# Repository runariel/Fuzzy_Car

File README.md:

# Fuzzy_Car
Planing to make a self driving car by Arduino

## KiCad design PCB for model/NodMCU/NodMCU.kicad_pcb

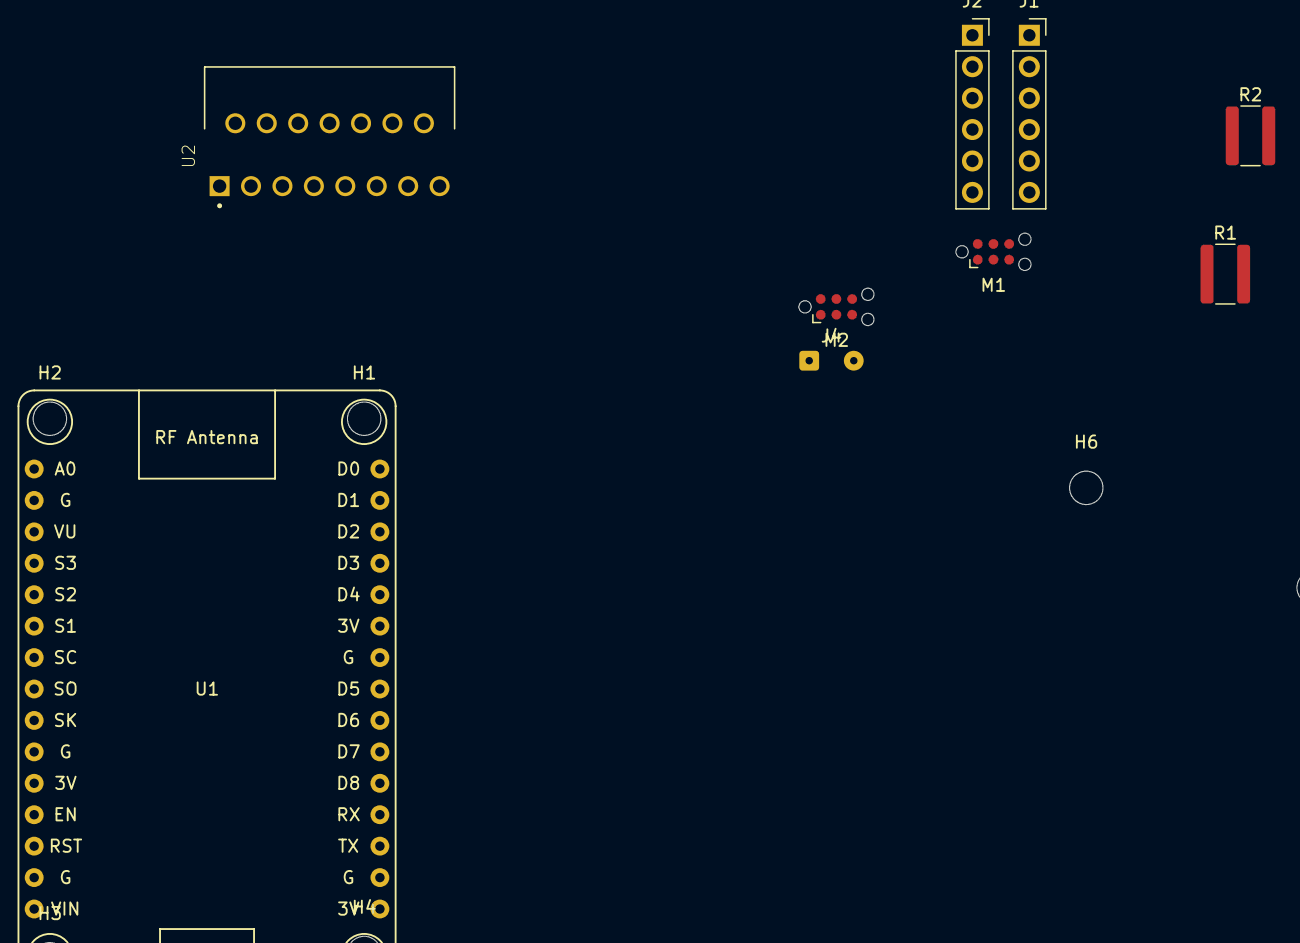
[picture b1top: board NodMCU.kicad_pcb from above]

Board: 2 copper layers, 21 parts (0 on the bottom side), 14 nets, no tracks yet.

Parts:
H1, H2, H3, H4, H5, H6, H7, H8, H9, H10, H11, H12: MountingHole; MountingHole_2.7mm
J1: VL53L0X Left; PinSocket_1x06_P2.54mm_Vertical
J2: VL53L0X Right; PinSocket_1x06_P2.54mm_Vertical
J4: Power supply; SolderWire-0.1sqmm_1x02_P3.6mm_D0.4mm_OD1mm
M1, M2: Motor_DC; Tag-Connect_TC2030-IDC-NL_2x03_P1.27mm_Vertical
R1, R2: 4.7k; R_1218_3246Metric
U1: NodeMCU_1.0_(ESP-12E); NodeMCU1.0(12-E)
U2: L298N; TO127P2020X500X2100-15

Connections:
5V: J1.1, J2.1, J4.1, R1.2, R2.2, U1.15, U2.9
EN_A: U1.23, U2.6
EN_B: U1.22, U2.11
GND: J1.2, J2.2, J4.2, U1.10, U1.14, U1.17, U1.24, U2.8
IN1_IN3: U1.27, U2.5, U2.10
IN2_IN4: U1.21, U2.7, U2.12
unnamed: M1.1, U2.2
unnamed: M1.2, U2.3
unnamed: M2.1, U2.13
unnamed: M2.2, U2.14
SCL: J1.3, J2.3, R1.1, U1.29
SDA: J1.4, J2.4, R2.1, U1.28
XSHUT_Left: J1.6, U1.26
XSHUT_Right: J2.6, U1.20

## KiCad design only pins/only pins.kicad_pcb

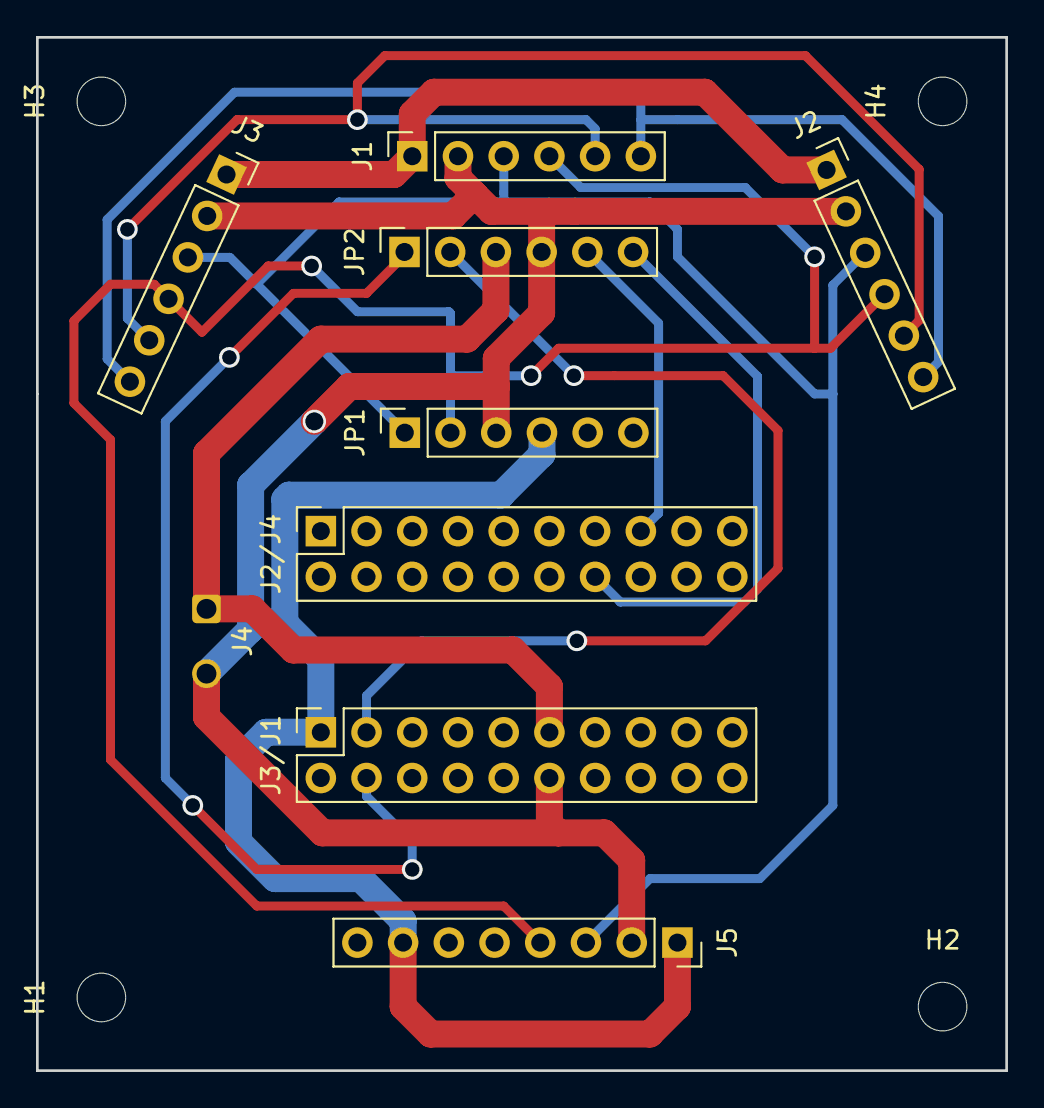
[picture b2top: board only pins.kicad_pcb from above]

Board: 2 copper layers, 53.8 x 57.4 mm, 13 parts (0 on the bottom side), 12 nets.

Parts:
H1, H2, H3, H4: MountingHole; MountingHole_2.7mm
J1, J2, J3: I2c; PinSocket_1x06_P2.54mm_Vertical
J2/J4, J3/J1: PinSocket_2x10_P2.54mm_Vertical
J4: Power supply; SolderWire-0.1sqmm_1x02_P3.6mm_D0.4mm_OD1mm
J5: gyro connector; PinSocket_1x08_P2.54mm_Vertical
JP1, JP2: M06SIP; PinSocket_1x06_P2.54mm_Vertical

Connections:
3.3V: J3/J1.1, J5.1, J5.7, JP1.4
5V: J3/J1.11, J4.1, JP2.3
/A0_RX: J3/J1.3, JP2.2
/A0_TX: J3/J1.4, JP2.1
/GPIO1: J1.5, J2.5, J3.5
/HV3: J2/J4.15, JP2.5
/HV4: J2/J4.14, JP2.6
/LV3: J1.4, J2.4, J3.4, J5.4, JP1.2
/LV4: J1.3, J2.3, J3.3, J5.3, JP1.1
/VIN: J1.1, J2.1, J3.1
/XShutDown: J1.6, J2.6, J3.6
GND: J1.2, J2.2, J3.2, J3/J1.12, J4.2, J5.2, JP1.3, JP2.4

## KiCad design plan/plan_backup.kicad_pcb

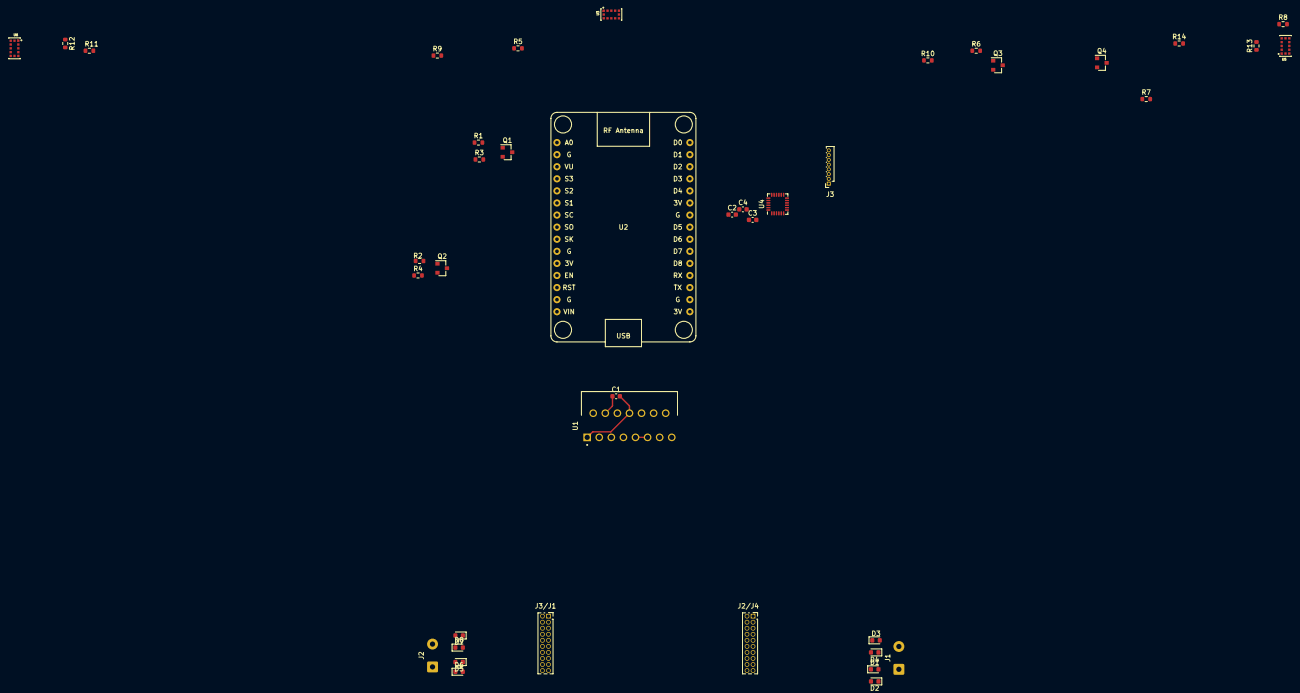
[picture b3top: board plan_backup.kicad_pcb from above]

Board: 2 copper layers, 41 parts (0 on the bottom side), 23 nets.

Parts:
C1: 220u; C_0603_1608Metric
C2: 0.01u; C_0603_1608Metric
C3: 0.1u; C_0603_1608Metric
C4: 2.2n; C_0603_1608Metric
D1, D2, D3, D4, D5, D6, D7, D8: D; D_0603_1608Metric
J1, J2: Conn_01x02_Female; SolderWire-0.5sqmm_1x02_P4.8mm_D0.9mm_OD2.3mm
J2/J4, J3/J1: PinSocket_2x10_P1.27mm_Vertical
J3: Conn_01x08_Female; PinSocket_1x08_P1.00mm_Vertical
Q1, Q2, Q3, Q4: BSS138; SOT-23
R1, R2, R3, R4, R5, R6, R7, R8, R9, R10, R11, R12, R13, R14: 10k; R_0603_1608Metric
U1: L298N; TO127P2020X500X2100-15
U2: NodeMCU_1.0_(ESP-12E); NodeMCU1.0(12-E)
U3, U5, U6: VL53L0CXV0DH_1; 1
U4: MPU-6050; InvenSense_QFN-24_4x4mm_P0.5mm

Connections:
3.3V: C2.2, J3.1, J3/J1.1, Q1.1, Q2.1, Q3.1, Q4.1, R3.2, R4.2, R5.2, R6.1, R8.2, R9.2, R10.2, R12.2, R13.1, R14.1, U2.7, U2.12, U2.15, U3.1, U3.1.1, U3.11, U4.8, U4.13, U5.1, U5.1.1, U5.11, U6.1, U6.1.1, U6.11
5V: J3/J1.11, U1.6, U1.9, U1.11
+7.5V: C1.1, D1.1, D3.1, D5.1, D7.1, U1.4
/P2-1_PWM: J2/J4.10, U1.5
/P6-0_PWM: J2/J4.9, U1.7
/P6-1_PWM: J2/J4.8, U1.10
/P6-2_PWM: J2/J4.7, U1.12
/lvl: J3.3, J3.4, Q1.2, Q2.2, Q3.2, Q4.2, R3.1, R4.1, R9.1, R12.1, U2.18, U2.19, U3.9, U3.10, U4.23, U4.24, U5.9, U5.10, U6.9, U6.10
GND: C1.2, C2.1, C3.1, C4.1, D2.2, D4.2, D6.2, D8.2, J2/J4.20, J3.2, J3.7, J3/J1.12, U1.1, U1.8, U2.17, U3.2, U3.3, U3.4, U3.6, U3.12, U4.1, U4.9, U4.11, U4.18, U5.2, U5.3, U5.4, U5.6, U5.12, U6.2, U6.3, U6.4, U6.6, U6.12
HV: J2/J4.14, J2/J4.15, J3/J1.15, J3/J1.16, Q1.3, Q2.3, Q3.3, Q4.3, R1.1, R1.2, R2.1, R2.2, R7.1, R7.2, R11.1, R11.2
unnamed: C3.2, U4.10
unnamed: C4.2, U4.20
unnamed: D1.2, D2.1, J1.1, U1.2
unnamed: D3.2, D4.1, J1.2, U1.3
unnamed: D5.2, D6.1, J2.1, U1.13
unnamed: D7.2, D8.1, J2.2, U1.14
unnamed: J3.5, U4.6
unnamed: J3.6, U4.7
unnamed: J3.8, U4.12
unnamed: R6.2, U3.7
unnamed: R13.2, U5.7
unnamed: R14.2, U6.7
XShutDown: R5.1, R8.1, R10.1, U3.5, U5.5, U6.5

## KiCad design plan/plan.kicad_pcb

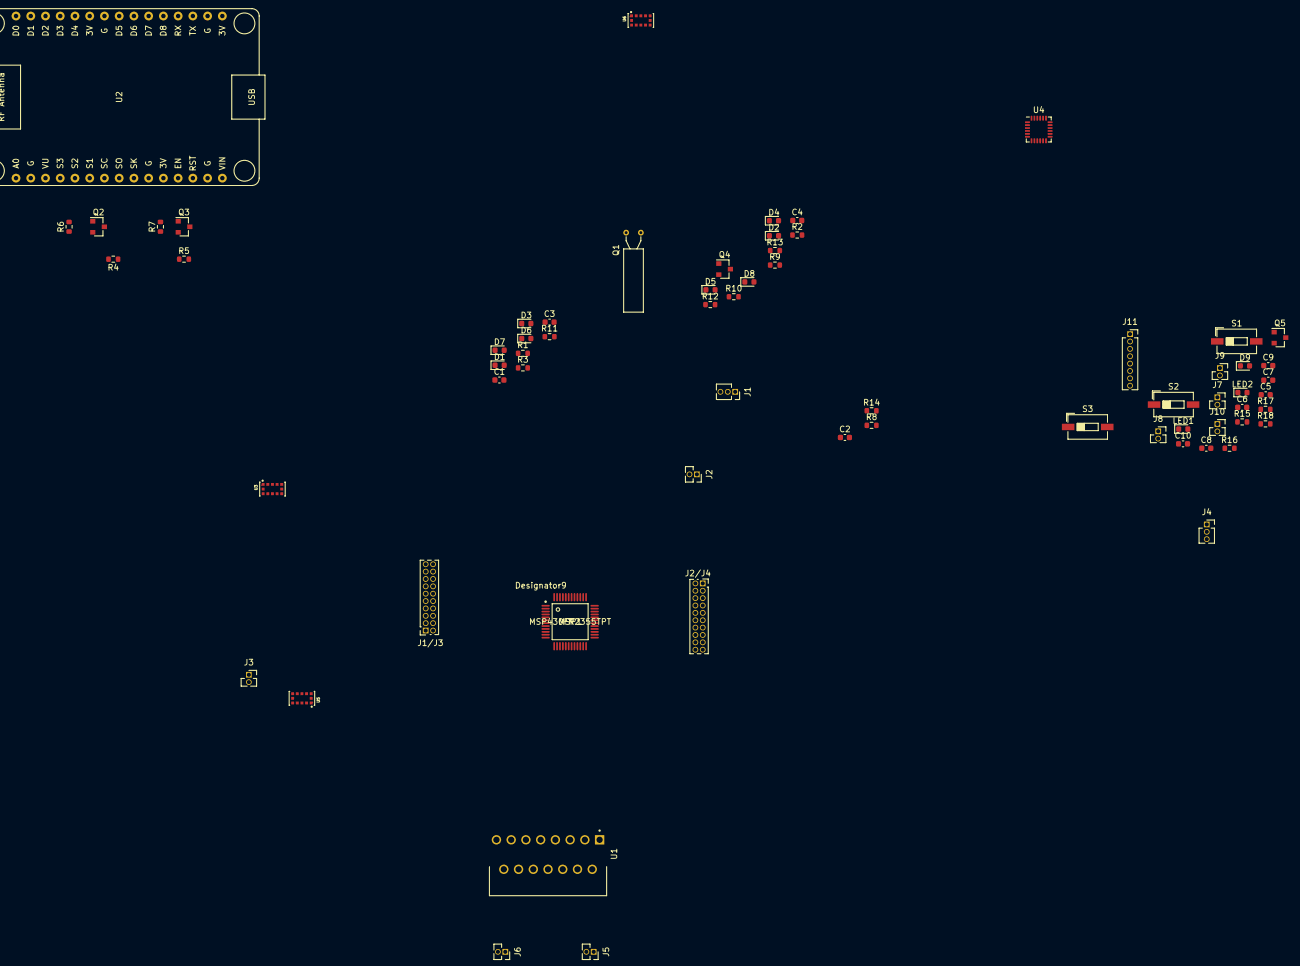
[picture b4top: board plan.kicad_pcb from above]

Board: 2 copper layers, 67 parts (0 on the bottom side), 50 nets, no tracks yet.

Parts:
C1, C2, C3, C4, C5, C7: C_0603_1608Metric
C6: 220u; C_0603_1608Metric
C8: 0.01u; C_0603_1608Metric
C9: 0.1u; C_0603_1608Metric
C10: 2.2n; C_0603_1608Metric
D1, D2, D3, D4, D5, D6, D7, D8: D; D_0603_1608Metric
D9: D_0603_1608Metric
J1, J4: PinSocket_1x03_P1.27mm_Vertical
J1/J3, J2/J4: PinSocket_2x10_P1.27mm_Vertical
J2, J3, J7, J8, J9, J10: PinSocket_1x02_P1.27mm_Vertical
J5, J6: Conn_01x02_Female; PinSocket_1x02_P1.27mm_Vertical
J11: Conn_01x08_Female; PinSocket_1x08_P1.27mm_Vertical
LED1: Red; LED_0603_1608Metric
LED2: Green; LED_0603_1608Metric
MSP1: MSP430FR2355TPT
Q1: Crystal_AT310_D3.0mm_L10.0mm_Horizontal
Q2, Q3, Q4, Q5: BSS138; SOT-23
R1, R2, R3, R8: R_0603_1608Metric
R4, R5, R6, R7, R9, R10, R11, R12, R13, R14, R15, R16, R17, R18: 10k; R_0603_1608Metric
S1, S2, S3: SW_DIP_SPSTx01_Slide_6.7x4.1mm_W6.73mm_P2.54mm_LowProfile_J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
U1: L298N; TO127P2020X500X2100-15
U2: NodeMCU_1.0_(ESP-12E); NodeMCU1.0(12-E)
U3, U5, U6: VL53L0CXV0DH_1; 1
U4: MPU-6050; InvenSense_QFN-24_4x4mm_P0.5mm

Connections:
3.3V: C1.2, C2.2, C3.1, C3.2, C4.1, C4.2, C5.1, C5.2, C6.2, C8.1, C8.2, C9.1, C10.1, D2.2, D4.2, D6.2, D8.2, D9.2, J1.1, J1.2, J1.3, J1/J3.1, J2/J4.16, J2/J4.20, J4.2, J4.3, J7.1, J7.2, J8.2, J11.1, J11.2, J11.7, LED1.2, LED2.2, MSP1.4, MSP1.5, MSP1.6, MSP1.7, Q2.1, Q3.1, Q4.1, Q5.1, R2.1, R2.2, R6.2, R7.2, R9.2, R10.1, R12.2, R13.2, R14.2, R16.2, R17.1, R18.1, S1.1, S1.2, S2.1, S2.2, S3.1, S3.2, U1.1, U1.8, U2.7, U2.12, U2.15, U2.17, U3.1, U3.1.1, U3.2, U3.3, U3.4, U3.6, U3.11, U3.12, U4.1, U4.8, U4.9, U4.11, U4.13, U4.18, U5.1, U5.1.1, U5.2, U5.3, U5.4, U5.6, U5.11, U5.12, U6.1, U6.1.1, U6.2, U6.3, U6.4, U6.6, U6.11, U6.12
5V: J4.1, U1.6, U1.9, U1.11
+7.5V: C6.1, D1.1, D3.1, D5.1, D7.1, U1.4
/32.768kHz: C1.1, MSP1.8, Q1.1
/A0_RX: J1/J3.3, MSP1.32
/A0_TX: J1/J3.4, MSP1.31
/A5: J1/J3.2, MSP1.33
/A10: J1/J3.6, MSP1.41
/B0_SCL: J1/J3.9, MSP1.48
/B0_SDA: J1/J3.10, MSP1.1
/B1_CLK: J1/J3.7, MSP1.14
/B1_CS: J2/J4.13, MSP1.15
/OA2+: J8.1, MSP1.44
/OA2-: J9.1, MSP1.45
/OA2O: J10.1, MSP1.46
/P1.0: J2.1, MSP1.3
/P2-1_PWM: MSP1.29, U1.5
/P2.0: J2/J4.19, MSP1.30
/P2.2: J2/J4.18, MSP1.28
/P2.5: J2/J4.12, MSP1.10
/P2.6: C2.1, MSP1.9, Q1.2
/P3.0: J2/J4.11, MSP1.47
/P3.4: J1/J3.8, MSP1.38
/P3.6: J1/J3.5, MSP1.36
/P4.0: J2/J4.17, MSP1.26
/P6-0_PWM: MSP1.22, U1.7
/P6-1_PWM: MSP1.21, U1.10
/P6-2_PWM: MSP1.20, U1.12
/P6.6: J3.1, MSP1.16
/lvl: J11.3, J11.4, Q2.2, Q3.2, Q4.2, Q5.2, R6.1, R7.1, R13.1, R16.1, U2.18, U2.19, U3.9, U3.10, U4.23, U4.24, U5.9, U5.10, U6.9, U6.10
HV: J2/J4.14, J2/J4.15, MSP1.12, MSP1.13, MSP1.42, MSP1.43, Q2.3, Q3.3, Q4.3, Q5.3, R4.1, R4.2, R5.1, R5.2, R11.1, R11.2, R15.1, R15.2
unnamed: C7.1, J10.2, R8.2
unnamed: C7.2, D9.1, J9.2, R8.1
unnamed: C9.2, U4.10
unnamed: C10.2, U4.20
unnamed: D1.2, D2.1, J5.1, U1.2
unnamed: D3.2, D4.1, J5.2, U1.3
unnamed: D5.2, D6.1, J6.1, U1.13
unnamed: D7.2, D8.1, J6.2, U1.14
unnamed: J2.2, R1.2
unnamed: J3.2, R3.2
unnamed: J11.5, U4.6
unnamed: J11.6, U4.7
unnamed: J11.8, U4.12
unnamed: LED1.1, R1.1
unnamed: LED2.1, R3.1
unnamed: R10.2, U3.7
unnamed: R17.2, U5.7
unnamed: R18.2, U6.7
XShutDown: R9.1, R12.1, R14.1, U3.5, U5.5, U6.5

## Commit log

2021-12-06 Uplaod Project V1
2021-12-10 model pcb
    Added the PCB which use the ESP8266 as CPU

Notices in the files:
parts and their libraries:
Copyright 2016 Accelerated Designs. All rights reserved.
